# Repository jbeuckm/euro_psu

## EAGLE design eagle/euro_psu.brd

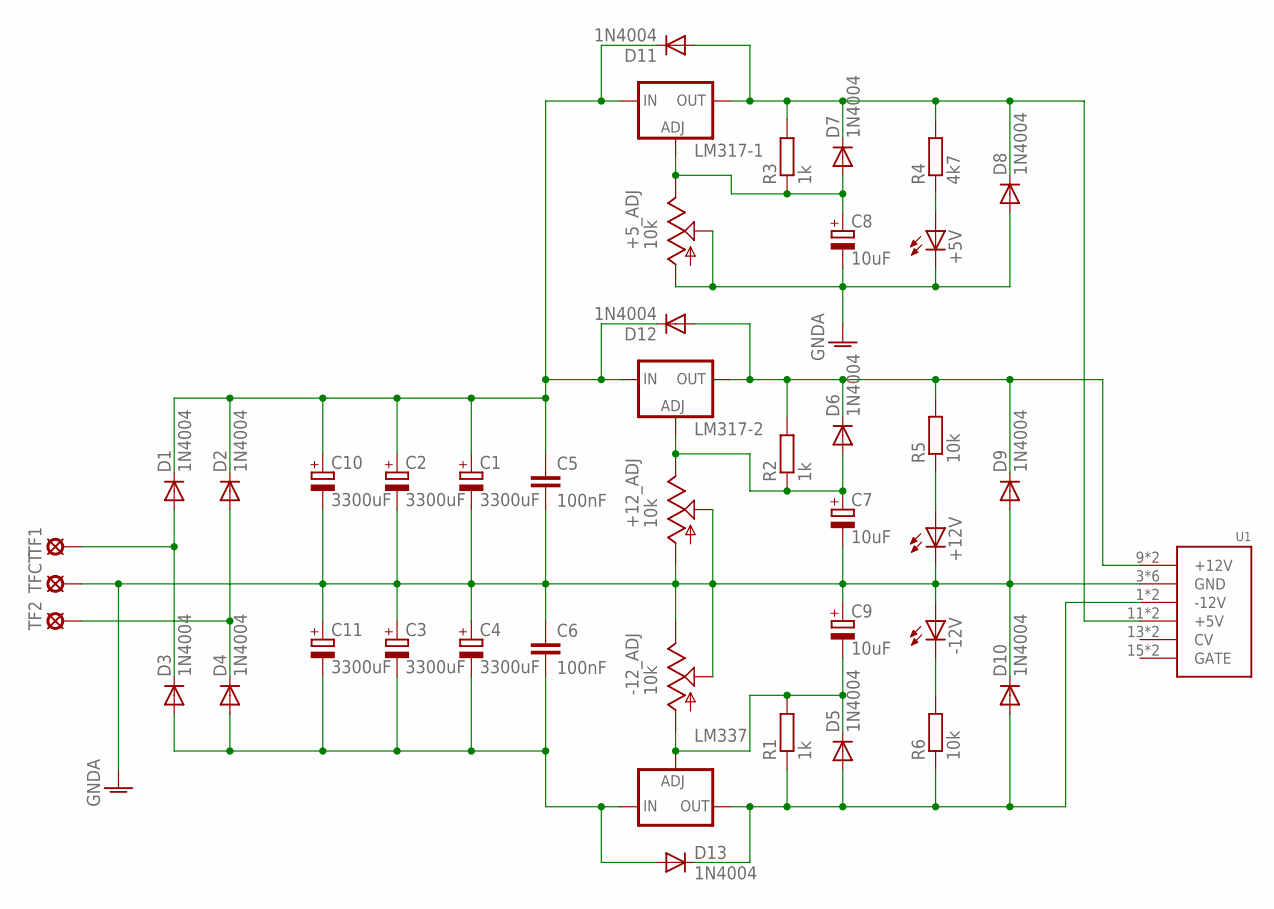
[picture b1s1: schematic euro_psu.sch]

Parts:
+5V, +12V: LED5MM
+5_ADJ, +12_ADJ: 10k; B64W
-12V: LED5MM
-12_ADJ: 10k; B64W
C1, C2, C3, C4, C10, C11: 3300uF; E7,5-16
C5, C6: 100nF; C025-025X050
C7, C8, C9: 10uF; B45181A
D1, D2, D3, D4, D5, D6, D7, D8, D9, D10, D11, D12, D13: 1N4004; DO41-10
LM317-1, LM317-2: LM317TS; 317TS
LM337: LM337TS; 337TS
R1, R2, R3: 1k; 0207/10
R4: 4k7; 0207/10
R5, R6: 10k; 0207/10
TF1, TF2: SE14
TFCT: SE14
U1: POWER; POWER_16

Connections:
GNDA: +5V.K (C), +5_ADJ.A, +5_ADJ.P$1 (S), +5_ADJ.S, +12V.K (C), +12_ADJ.A, +12_ADJ.P$1 (S), +12_ADJ.S, -12V.A, -12_ADJ.E, -12_ADJ.P$1 (S), -12_ADJ.S, C1.-, C2.-, C3.+, C4.+, C5.2, C6.1, C7.-, C8.-, C9.+, C10.-, C11.+, D8.A, D9.A, D10.C, TFCT.MP, U1.3 (GND), U1.4 (GND), U1.5 (GND), U1.6 (GND), U1.7 (GND), U1.8 (GND)
unnamed: D1.A, D3.C, TF1.MP
unnamed: D2.A, D4.C, TF2.MP
unnamed: C3.-, C4.-, C6.2, C11.-, D3.A, D4.A, D13.A, LM337.2 (IN)
unnamed: C1.+, C2.+, C5.1, C10.+, D1.C, D2.C, D11.C, D12.C, LM317-1.3 (IN), LM317-2.3 (IN)
unnamed: -12_ADJ.A, C9.-, D5.C, LM337.1 (ADJ), R1.2
unnamed: +12_ADJ.E, C7.+, D6.A, LM317-2.1 (ADJ), R2.1
unnamed: +5_ADJ.E, C8.+, D7.A, LM317-1.1 (ADJ), R3.1
unnamed: D5.A, D10.A, D13.C, LM337.3 (OUT), R1.1, R6.1, U1.1 (-12V), U1.2 (-12V)
unnamed: D6.C, D9.C, D12.A, LM317-2.2 (OUT), R2.2, R5.2, U1.9 (+12V), U1.10 (+12V)
unnamed: D7.C, D8.C, D11.A, LM317-1.2 (OUT), R3.2, R4.2, U1.11 (+5V), U1.12 (+5V)
unnamed: +5V.A, R4.1
unnamed: -12V.K (C), R6.2
unnamed: +12V.A, R5.1

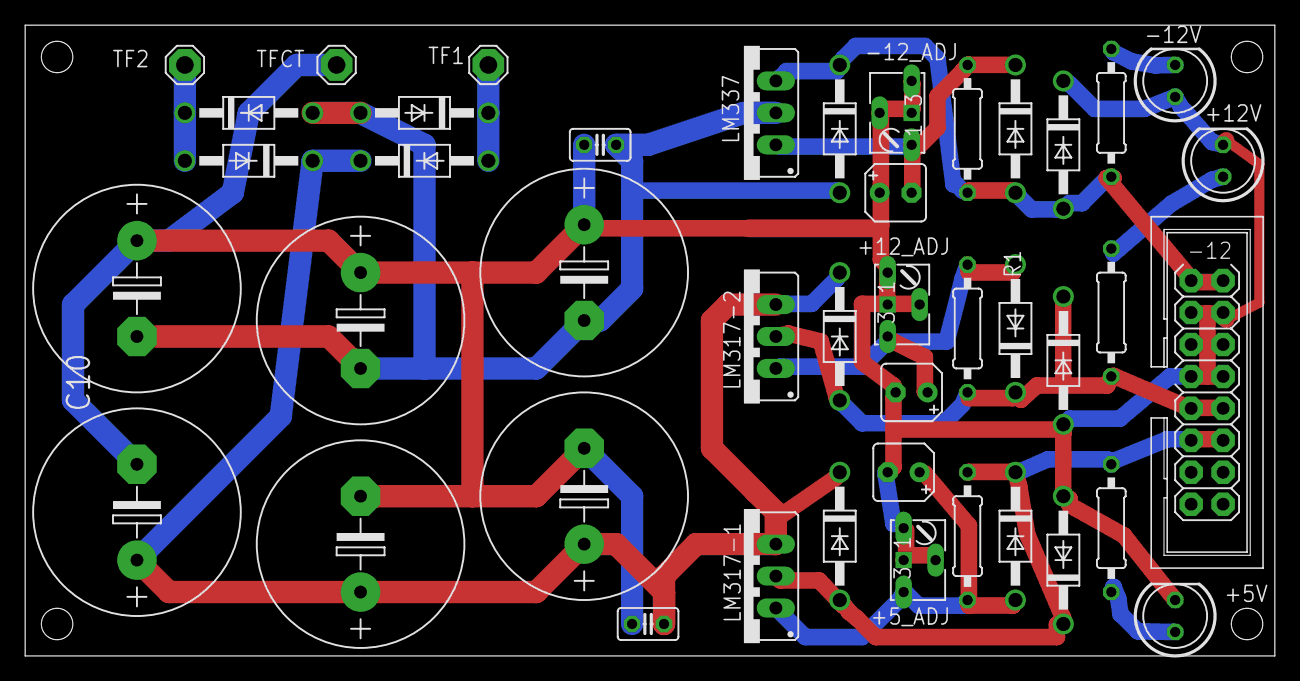
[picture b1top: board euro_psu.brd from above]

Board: 2 copper layers, 99.4 x 50.2 mm, 43 parts (0 on the bottom side), 14 nets.

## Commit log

2018-01-13 silkscreen draft
2018-01-13 rerouted with regulator protection diodes
2018-01-14 vector silkscreen
2018-01-15 tweaked for more space behind the regulators
2018-01-15 gerbers
